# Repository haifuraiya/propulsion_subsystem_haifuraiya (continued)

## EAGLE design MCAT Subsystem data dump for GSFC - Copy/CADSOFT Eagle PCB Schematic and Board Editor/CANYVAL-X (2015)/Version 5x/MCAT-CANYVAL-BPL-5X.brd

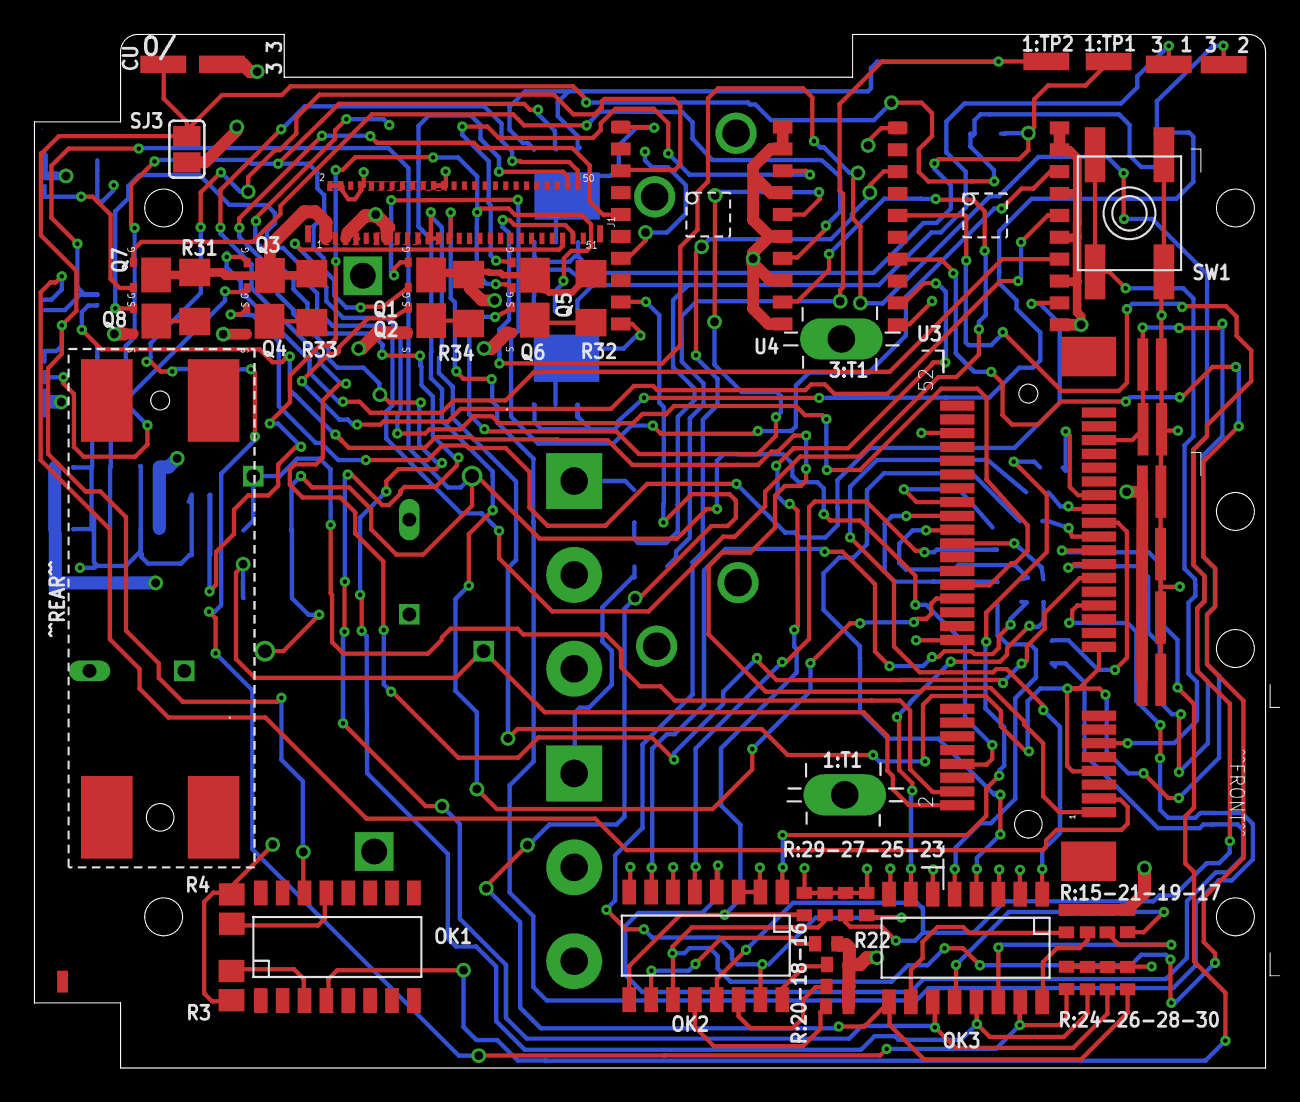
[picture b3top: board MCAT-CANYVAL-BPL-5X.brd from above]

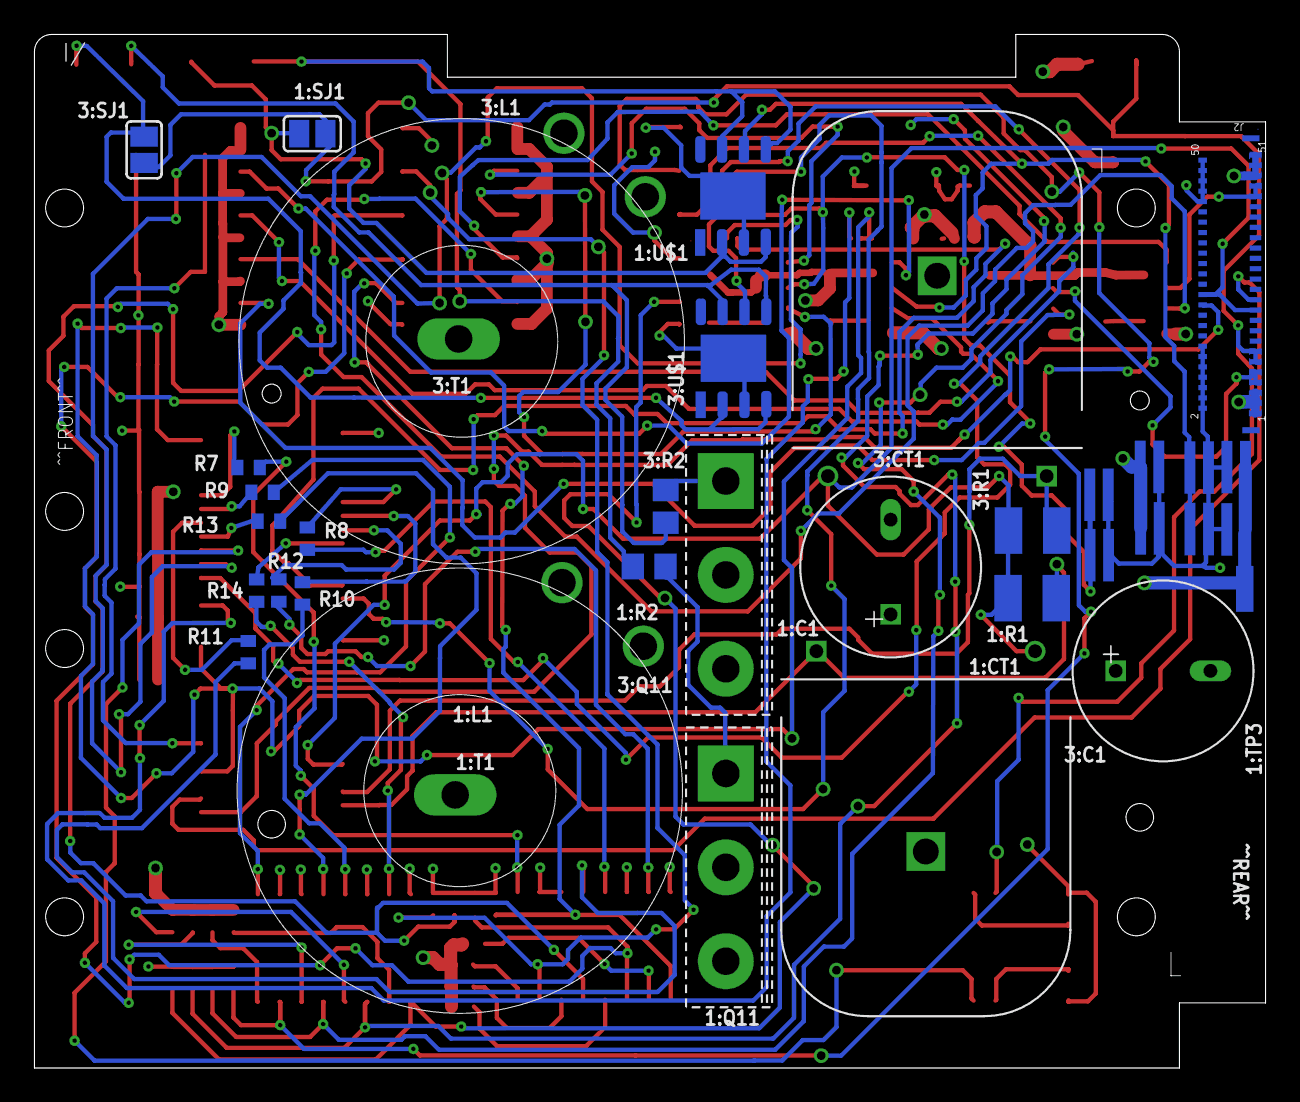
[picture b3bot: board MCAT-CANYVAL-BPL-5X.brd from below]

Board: 6 copper layers, 71.5 x 60.0 mm, 95 parts (34 on the bottom side), 78 nets.

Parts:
B2: MCAT-4CU-C-PCB/BPL; MCAT-4CU-C-BPL-V4-BLANK
CU-V2L1-1:BC3: BYPASS-CAP-1UF; 0612-REV
CU-V2L1-1:BC4: BYPASS-CAP-0.1UF; 0612-REV
CU-V2L1-1:J7: LATCH_NANO54415_MODULE; LATCH_SD-48099-400
CU-V2L1-1:J9: CONN_NANO54415_MODULE; CONN_SD-67910-001
CU-V2L1-1:OK1: PS2801C-4; SSOP(16PIN)
CU-V2L1-1:R3: 560R; R0805
CU-V2L1-1:R4: 1K2; R0805
CU-V2L1-1:SJ3: 0R; SJ
CU-V2L1-1:SW1: SPST_TACT-EVQQ2; EVQ-Q2
CU-V2L1-1:TP1: PCB-MINI-SMD-TESTPOINT/SQ; PCB-MINI-SMD-TESTPOINT
F1, F2, F3, F4, F5, F6: SMTRAM2-6-5-RA; SMTRA-M2-6-5-RA
J1, J2: MOLEX-502598-5193
PD-V2L1-1:BC1, PD-V2L1-1:BC4: BYPASS-CAP-0.1UF; 0612-REV
PD-V2L1-1:BC2, PD-V2L1-1:BC3: BYPASS-CAP-1UF; 0612-REV
PD-V2L1-1:OK2, PD-V2L1-1:OK3: PS2801C-4; SSOP(16PIN)
PD-V2L1-1:Q1, PD-V2L1-1:Q2, PD-V2L1-1:Q3, PD-V2L1-1:Q4, PD-V2L1-1:Q5, PD-V2L1-1:Q6, PD-V2L1-1:Q7, PD-V2L1-1:Q8: SI5404BDC; 1206-8-CHIPFET
PD-V2L1-1:R7, PD-V2L1-1:R8, PD-V2L1-1:R9, PD-V2L1-1:R10, PD-V2L1-1:R11, PD-V2L1-1:R12, PD-V2L1-1:R13: 5K42; R0402
PD-V2L1-1:R14: 5K42%; R0402
PD-V2L1-1:R15, PD-V2L1-1:R16, PD-V2L1-1:R17, PD-V2L1-1:R18, PD-V2L1-1:R19, PD-V2L1-1:R20, PD-V2L1-1:R21, PD-V2L1-1:R22: 100k; R0402
PD-V2L1-1:R23, PD-V2L1-1:R24, PD-V2L1-1:R25, PD-V2L1-1:R26, PD-V2L1-1:R27, PD-V2L1-1:R28, PD-V2L1-1:R29, PD-V2L1-1:R30: 51k; R0402
PD-V2L1-1:R31, PD-V2L1-1:R32, PD-V2L1-1:R33, PD-V2L1-1:R34: 0.1R; R1206
PD-V2L1-1:U3, PD-V2L1-1:U4: LT1161ISW; 20-LEAD-PLASTIC-SO
PPU-V8C1-1:BC1, PPU-V8C1-1:BC3, PPU-V8C1-3:BC1, PPU-V8C1-3:BC3: BYPASS-CAP-0.1UF; 0612-REV
PPU-V8C1-1:BC2, PPU-V8C1-1:BC4, PPU-V8C1-3:BC2, PPU-V8C1-3:BC4: BYPASS-CAP-1UF; 0612-REV
PPU-V8C1-1:C1, PPU-V8C1-3:C1: 680uF/20WV; CHEMI-CON-PSG-JB5
PPU-V8C1-1:CT1, PPU-V8C1-3:CT1: MURATA-5600-CURR-XFR/RA; MURATA-5600-SERIES-CURR-XFR-RA
PPU-V8C1-1:L1, PPU-V8C1-3:L1: PPUV8-INDUCTOR-V2
PPU-V8C1-1:Q11, PPU-V8C1-3:Q11: IXYH30N120C3D1; IXYS-TO-247-AD-VERT
PPU-V8C1-1:R1, PPU-V8C1-3:R1: 15R; R1210
PPU-V8C1-1:R2, PPU-V8C1-3:R2: 1K; R0805
PPU-V8C1-1:SJ1, PPU-V8C1-3:SJ1: 0R; SJ
PPU-V8C1-1:T1, PPU-V8C1-3:T1: MCAT-SPADE-TERMINAL; SPADE-TERMINAL-FLANGED-NYLON-INSULATED
PPU-V8C1-1:TP1, PPU-V8C1-1:TP2, PPU-V8C1-1:TP3, PPU-V8C1-3:TP1, PPU-V8C1-3:TP2, PPU-V8C1-3:TP3: PCB-MINI-SMD-TESTPOINT/SQ; PCB-MINI-SMD-TESTPOINT
PPU-V8C1-1:U$1, PPU-V8C1-3:U$1: IXDN604/SI; IXYS-SI-8PIN-POWER-SOIC

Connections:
AGND_ADC_GROUND: CU-V2L1-1:J9.8, J2.21, J2.24, PPU-V8C1-1:CT1.3, PPU-V8C1-1:R1.2, PPU-V8C1-3:CT1.3, PPU-V8C1-3:R1.2
CH1_P18H: PD-V2L1-1:Q2.S, PPU-V8C1-1:BC1.1, PPU-V8C1-1:BC2.1, PPU-V8C1-1:C1.POS, PPU-V8C1-1:L1.1, PPU-V8C1-1:TP3.1
CH1_P18L: PD-V2L1-1:Q1.S, PPU-V8C1-1:BC3.1, PPU-V8C1-1:BC4.1, PPU-V8C1-1:U$1.6
CH1_SENSE+: CU-V2L1-1:J9.2, PPU-V8C1-1:CT1.1, PPU-V8C1-1:R1.1
CH2_P18H: J2.1, J2.3, J2.5, PD-V2L1-1:Q4.S
CH2_P18L: J2.7, J2.9, PD-V2L1-1:Q3.S
CH2_SENSE+: CU-V2L1-1:J9.1, J2.22
CH3_P18H: PD-V2L1-1:Q6.S, PPU-V8C1-3:BC1.1, PPU-V8C1-3:BC2.1, PPU-V8C1-3:C1.POS, PPU-V8C1-3:L1.1, PPU-V8C1-3:TP3.1
CH3_P18L: PD-V2L1-1:Q5.S, PPU-V8C1-3:BC3.1, PPU-V8C1-3:BC4.1, PPU-V8C1-3:U$1.6
CH3_SENSE+: CU-V2L1-1:J9.4, PPU-V8C1-3:CT1.1, PPU-V8C1-3:R1.1
CH4_P18H: J2.47, J2.49, J2.51, PD-V2L1-1:Q8.S
CH4_P18L: J2.43, J2.45, PD-V2L1-1:Q7.S
CH4_SENSE+: CU-V2L1-1:J9.3, J2.23
CU-V2L1-1:!RSTI: CU-V2L1-1:J9.11, CU-V2L1-1:SW1.A, CU-V2L1-1:SW1.A'
CU-V2L1-1:N$1: CU-V2L1-1:OK1.3, CU-V2L1-1:R3.2
CU-V2L1-1:N$2: CU-V2L1-1:OK1.13, CU-V2L1-1:R4.2
CU-V2L1-1:SW_TP1: CU-V2L1-1:J9.31, CU-V2L1-1:OK1.4
GND: CU-V2L1-1:BC3.2, CU-V2L1-1:BC4.2, CU-V2L1-1:J9.18, CU-V2L1-1:J9.48, CU-V2L1-1:R3.1, CU-V2L1-1:R4.1, CU-V2L1-1:SW1.B, CU-V2L1-1:SW1.B', J1.2, J1.4, J1.8, J1.10, J1.12, J1.14, J1.16, J1.18, J1.20, J1.22, J1.24, J2.2, J2.4, J2.6, J2.8, J2.10, J2.12, J2.14, J2.42, J2.44, J2.46, J2.48, J2.50, PD-V2L1-1:BC1.2, PD-V2L1-1:BC2.2, PD-V2L1-1:BC3.2, PD-V2L1-1:BC4.2, PD-V2L1-1:OK2.2, PD-V2L1-1:OK2.3, PD-V2L1-1:OK2.6, PD-V2L1-1:OK2.8, PD-V2L1-1:OK3.2, PD-V2L1-1:OK3.3, PD-V2L1-1:OK3.6, PD-V2L1-1:OK3.8, PD-V2L1-1:R23.1, PD-V2L1-1:R24.1, PD-V2L1-1:R25.1, PD-V2L1-1:R26.1, PD-V2L1-1:R27.1, PD-V2L1-1:R28.1, PD-V2L1-1:R29.1, PD-V2L1-1:R30.1, PD-V2L1-1:U3.1, PD-V2L1-1:U3.10, PD-V2L1-1:U4.1, PD-V2L1-1:U4.10, PPU-V8C1-1:BC1.2, PPU-V8C1-1:BC2.2, PPU-V8C1-1:BC3.2, PPU-V8C1-1:BC4.2, PPU-V8C1-1:C1.NEG, PPU-V8C1-1:CT1.PPU-K, PPU-V8C1-1:Q11.E, PPU-V8C1-1:U$1.3, PPU-V8C1-1:U$1.9, PPU-V8C1-3:BC1.2, PPU-V8C1-3:BC2.2, PPU-V8C1-3:BC3.2, PPU-V8C1-3:BC4.2, PPU-V8C1-3:C1.NEG, PPU-V8C1-3:CT1.PPU-K, PPU-V8C1-3:Q11.E, PPU-V8C1-3:U$1.3, PPU-V8C1-3:U$1.9
MCAT_SCL: CU-V2L1-1:J9.27, J1.50
MCAT_SDA: CU-V2L1-1:J9.29, J1.49
unnamed: CU-V2L1-1:J9.33, PD-V2L1-1:R13.2
P3: CU-V2L1-1:BC3.1, CU-V2L1-1:BC4.1, CU-V2L1-1:J9.7, CU-V2L1-1:J9.17, CU-V2L1-1:J9.47, J1.21, J1.23
PD-V2L1-1:CH1HG: PD-V2L1-1:Q2.G, PD-V2L1-1:U3.16
PD-V2L1-1:CH1LG: PD-V2L1-1:Q1.G, PD-V2L1-1:U3.18
PD-V2L1-1:CH1S: PD-V2L1-1:Q2.D, PD-V2L1-1:R34.1
PD-V2L1-1:CH2HG: PD-V2L1-1:Q4.G, PD-V2L1-1:U3.12
PD-V2L1-1:CH2LG: PD-V2L1-1:Q3.G, PD-V2L1-1:U3.14
PD-V2L1-1:CH2S: PD-V2L1-1:Q4.D, PD-V2L1-1:R33.1
PD-V2L1-1:CH3HG: PD-V2L1-1:Q6.G, PD-V2L1-1:U4.16
PD-V2L1-1:CH3LG: PD-V2L1-1:Q5.G, PD-V2L1-1:U4.18
PD-V2L1-1:CH3S: PD-V2L1-1:Q6.D, PD-V2L1-1:R32.1
PD-V2L1-1:CH4HG: PD-V2L1-1:Q8.G, PD-V2L1-1:U4.12
PD-V2L1-1:CH4LG: PD-V2L1-1:Q7.G, PD-V2L1-1:U4.14
PD-V2L1-1:CH4S: PD-V2L1-1:Q8.D, PD-V2L1-1:R31.1
PD-V2L1-1:N$4: PD-V2L1-1:OK2.16, PD-V2L1-1:R16.2
PD-V2L1-1:N$5: PD-V2L1-1:OK2.14, PD-V2L1-1:R18.2
PD-V2L1-1:N$7: PD-V2L1-1:OK2.12, PD-V2L1-1:R20.2
PD-V2L1-1:N$9: PD-V2L1-1:OK2.10, PD-V2L1-1:R22.2
PD-V2L1-1:N$10: PD-V2L1-1:OK3.16, PD-V2L1-1:R21.2
PD-V2L1-1:N$11: PD-V2L1-1:OK3.14, PD-V2L1-1:R19.2
PD-V2L1-1:N$12: PD-V2L1-1:OK3.12, PD-V2L1-1:R17.2
PD-V2L1-1:N$13: PD-V2L1-1:OK3.10, PD-V2L1-1:R15.2
PD-V2L1-1:OK1E1: PD-V2L1-1:OK2.15, PD-V2L1-1:R23.2, PD-V2L1-1:U3.3
PD-V2L1-1:OK1E2: PD-V2L1-1:OK2.13, PD-V2L1-1:R25.2, PD-V2L1-1:U3.5
PD-V2L1-1:OK1E3: PD-V2L1-1:OK2.11, PD-V2L1-1:R27.2, PD-V2L1-1:U3.7
PD-V2L1-1:OK1E4: PD-V2L1-1:OK2.9, PD-V2L1-1:R29.2, PD-V2L1-1:U3.9
PD-V2L1-1:OK2E1: PD-V2L1-1:OK3.15, PD-V2L1-1:R24.2, PD-V2L1-1:U4.3
PD-V2L1-1:OK2E2: PD-V2L1-1:OK3.13, PD-V2L1-1:R26.2, PD-V2L1-1:U4.5
PD-V2L1-1:OK2E3: PD-V2L1-1:OK3.11, PD-V2L1-1:R28.2, PD-V2L1-1:U4.7
PD-V2L1-1:OK2E4: PD-V2L1-1:OK3.9, PD-V2L1-1:R30.2, PD-V2L1-1:U4.9
PD-V2L1-1:P18_SW1: PD-V2L1-1:OK2.1, PD-V2L1-1:R7.1
PD-V2L1-1:P18_SW2: PD-V2L1-1:OK2.5, PD-V2L1-1:R8.1
PD-V2L1-1:P18_SW3: PD-V2L1-1:OK3.1, PD-V2L1-1:R9.1
PD-V2L1-1:P18_SW4: PD-V2L1-1:OK3.5, PD-V2L1-1:R10.1
PD-V2L1-1:P18_SW5: PD-V2L1-1:OK2.4, PD-V2L1-1:R11.1
PD-V2L1-1:P18_SW6: PD-V2L1-1:OK2.7, PD-V2L1-1:R12.1
PD-V2L1-1:P18_SW7: PD-V2L1-1:OK3.4, PD-V2L1-1:R13.1
PD-V2L1-1:P18_SW8: PD-V2L1-1:OK3.7, PD-V2L1-1:R14.1
PPU-V8C1-1:N$2: PPU-V8C1-1:Q11.G, PPU-V8C1-1:R2.2
PPU-V8C1-1:PPU-A: PPU-V8C1-1:L1.2, PPU-V8C1-1:Q11.C, PPU-V8C1-1:T1.T
PPU-V8C1-1:TPIPD_IN: PPU-V8C1-1:SJ1.2, PPU-V8C1-1:TP1.1, PPU-V8C1-1:U$1.2, PPU-V8C1-1:U$1.4
PPU-V8C1-1:TPIPD_OUT: PPU-V8C1-1:R2.1, PPU-V8C1-1:TP2.1, PPU-V8C1-1:U$1.5, PPU-V8C1-1:U$1.7
PPU-V8C1-3:N$2: PPU-V8C1-3:Q11.G, PPU-V8C1-3:R2.2
PPU-V8C1-3:PPU-A: PPU-V8C1-3:L1.2, PPU-V8C1-3:Q11.C, PPU-V8C1-3:T1.T
PPU-V8C1-3:TPIPD_IN: PPU-V8C1-3:SJ1.2, PPU-V8C1-3:TP1.1, PPU-V8C1-3:U$1.2, PPU-V8C1-3:U$1.4
PPU-V8C1-3:TPIPD_OUT: PPU-V8C1-3:R2.1, PPU-V8C1-3:TP2.1, PPU-V8C1-3:U$1.5, PPU-V8C1-3:U$1.7
SW_P18H1: CU-V2L1-1:J9.35, PD-V2L1-1:R11.2
SW_P18H3: CU-V2L1-1:J9.34, PD-V2L1-1:R12.2
SW_P18H4: CU-V2L1-1:J9.32, PD-V2L1-1:R14.2
SW_P18L: CU-V2L1-1:J9.39, PD-V2L1-1:R7.2
SW_P18L2: CU-V2L1-1:J9.38, PD-V2L1-1:R8.2
SW_P18L3: CU-V2L1-1:J9.37, PD-V2L1-1:R9.2
SW_P18L4: CU-V2L1-1:J9.36, PD-V2L1-1:R10.2
SW_RUNPMA: CU-V2L1-1:J9.23, J1.25
TP1_OUT: CU-V2L1-1:OK1.14, CU-V2L1-1:SJ3.2, CU-V2L1-1:TP1.1, J2.11, J2.13, PPU-V8C1-1:SJ1.1, PPU-V8C1-3:SJ1.1
UART0_RX: CU-V2L1-1:J9.24, J1.48
UART0_TX: CU-V2L1-1:J9.26, J1.47
VOUTA: CU-V2L1-1:SJ3.1, J1.1, J1.3, J1.5, J1.7, J1.11, J1.13, J1.15, J1.17, J1.19, PD-V2L1-1:BC1.1, PD-V2L1-1:BC2.1, PD-V2L1-1:BC3.1, PD-V2L1-1:BC4.1, PD-V2L1-1:Q1.D, PD-V2L1-1:Q3.D, PD-V2L1-1:Q5.D, PD-V2L1-1:Q7.D, PD-V2L1-1:R15.1, PD-V2L1-1:R16.1, PD-V2L1-1:R17.1, PD-V2L1-1:R18.1, PD-V2L1-1:R19.1, PD-V2L1-1:R20.1, PD-V2L1-1:R21.1, PD-V2L1-1:R22.1, PD-V2L1-1:R31.2, PD-V2L1-1:R32.2, PD-V2L1-1:R33.2, PD-V2L1-1:R34.2, PD-V2L1-1:U3.11, PD-V2L1-1:U3.13, PD-V2L1-1:U3.15, PD-V2L1-1:U3.17, PD-V2L1-1:U3.19, PD-V2L1-1:U3.20, PD-V2L1-1:U4.11, PD-V2L1-1:U4.13, PD-V2L1-1:U4.15, PD-V2L1-1:U4.17, PD-V2L1-1:U4.19, PD-V2L1-1:U4.20

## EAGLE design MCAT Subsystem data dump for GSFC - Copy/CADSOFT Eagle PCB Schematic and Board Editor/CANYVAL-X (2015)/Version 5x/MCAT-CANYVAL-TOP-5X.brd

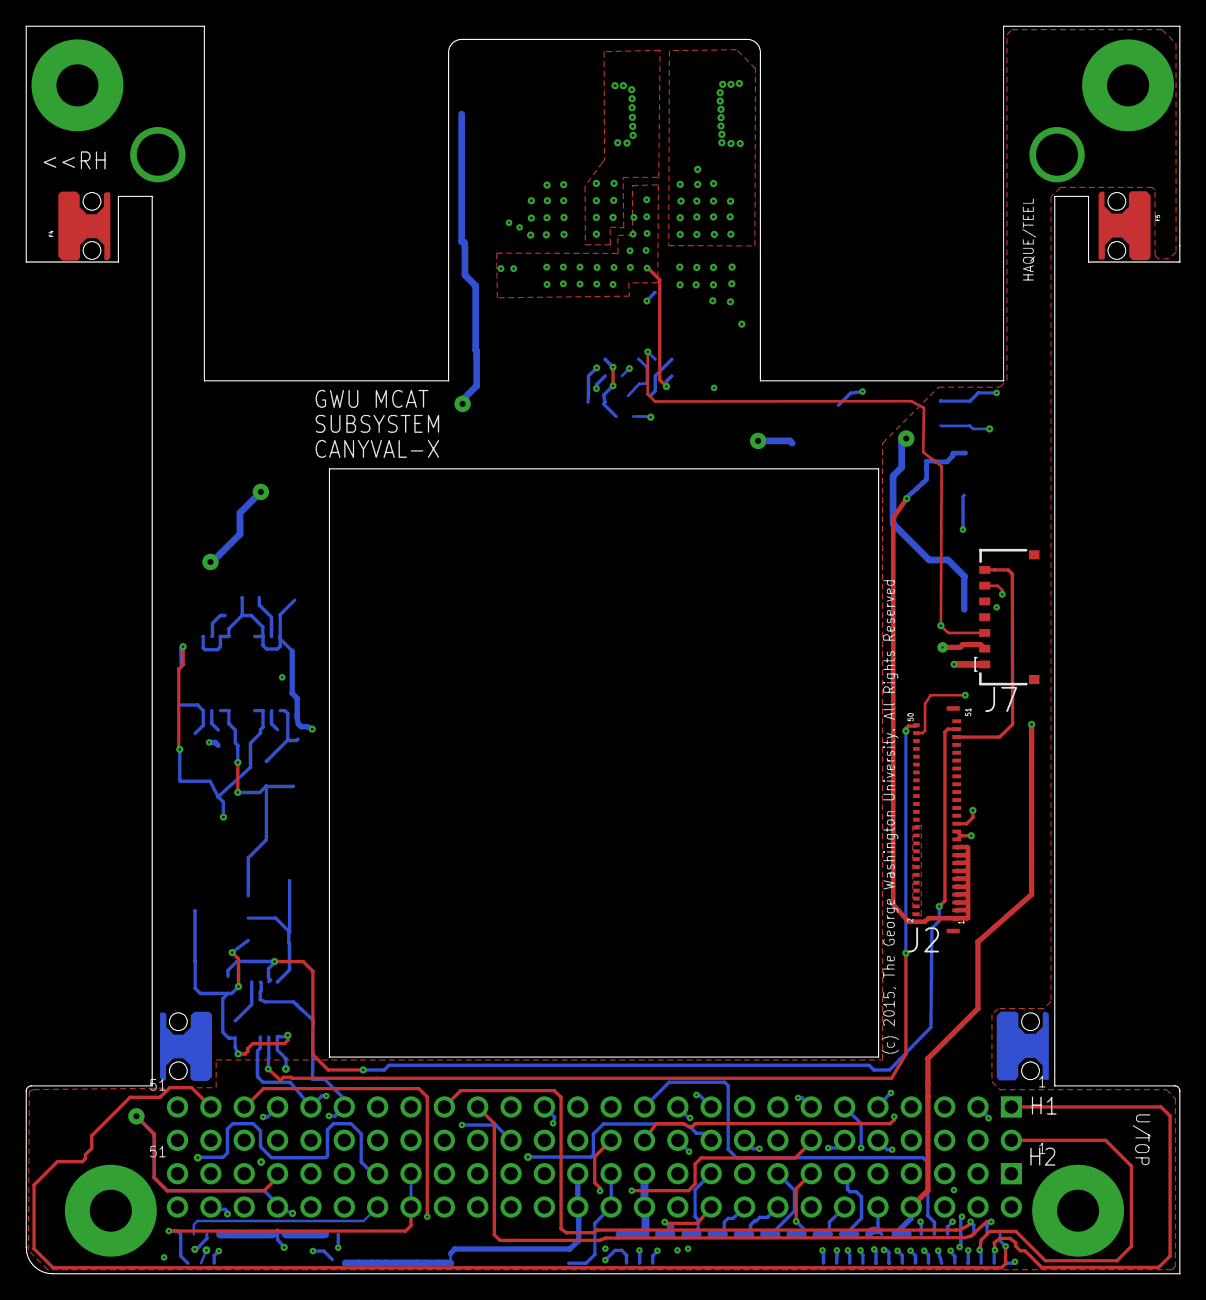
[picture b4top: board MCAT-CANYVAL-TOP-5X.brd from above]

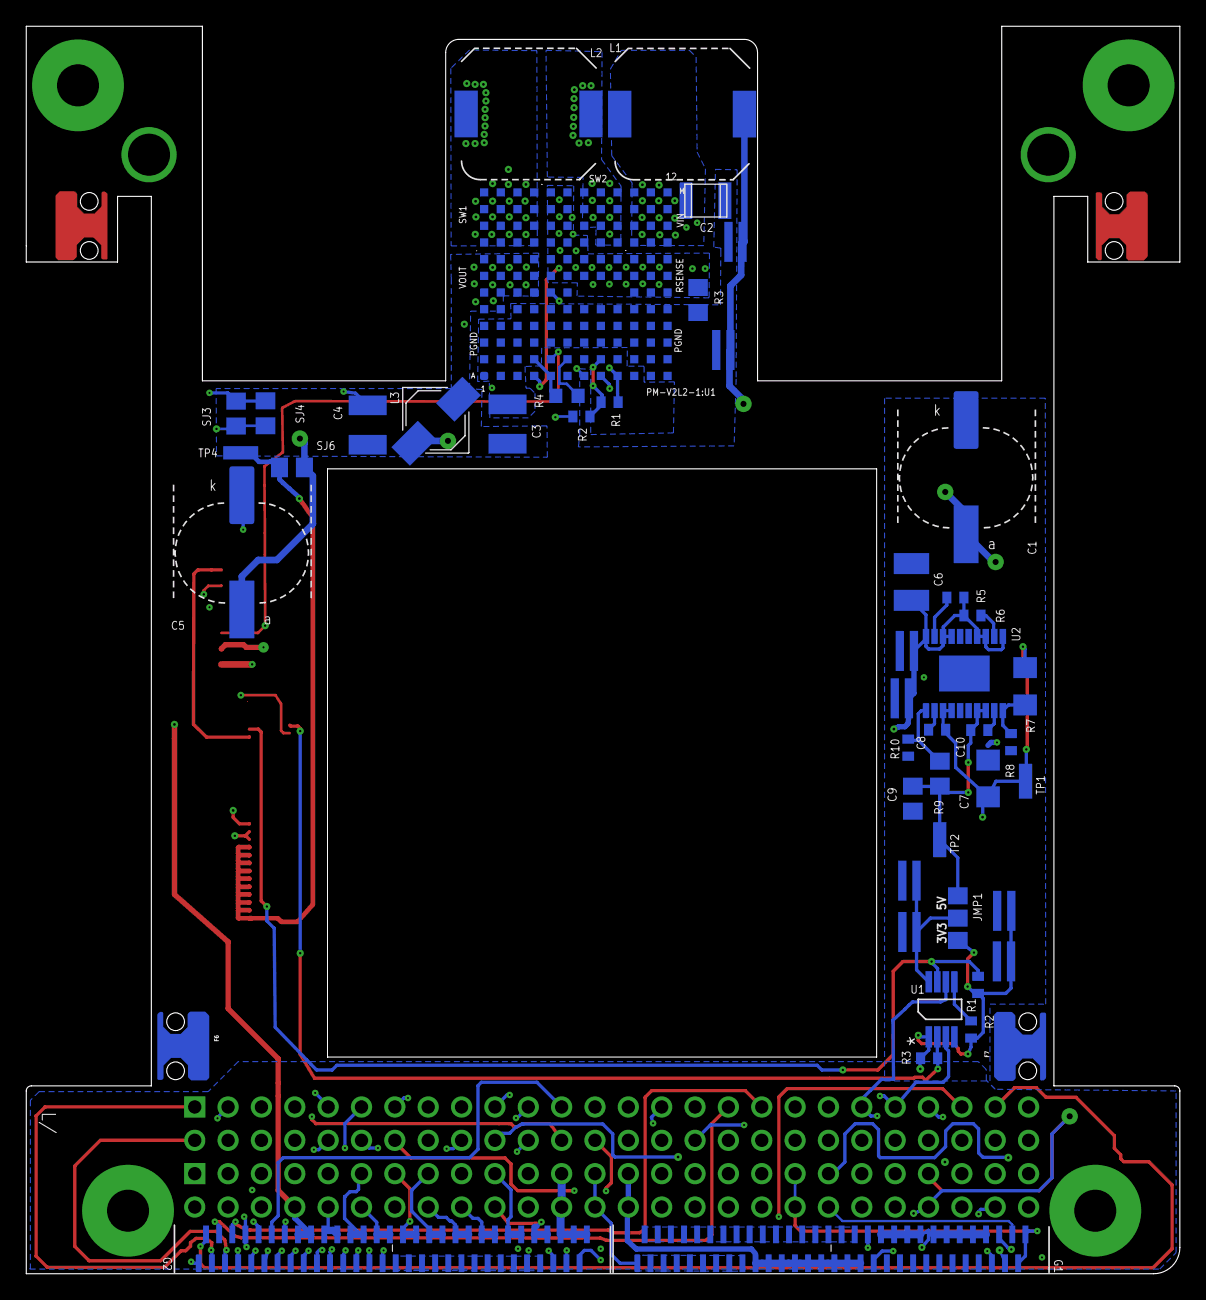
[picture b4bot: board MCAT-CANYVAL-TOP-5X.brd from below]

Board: 6 copper layers, 87.9 x 95.0 mm, 55 parts (48 on the bottom side), 72 nets.

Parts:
B8: MCAT-4CU-C-PCB/TOP; MCAT-4CU-C-TOP-V4-BLANK
CT-V2L1-1:BC3, CT-V2L1-1:BC5: BYPASS-CAP-1UF; 0612-REV
CT-V2L1-1:BC4, CT-V2L1-1:BC6: BYPASS-CAP-0.1UF; 0612-REV
CT-V2L1-1:J7: MOLEX-78171-5007
CT-V2L1-1:JMP1: 0R-JUMPA; A0R-JMP
CT-V2L1-1:R1, CT-V2L1-1:R2, CT-V2L1-1:R3: 10k; R0402
CT-V2L1-1:U1: PCA9512ADP; SOT505-1
F4, F5, F6, F7: SMTRAM2-6-5; SMTRA-M2-6-5
GBUS-TOP1:G1, GBUS-TOP1:G2: HIROSE-FH40-60S-0.5SV
GBUS-TOP1:H1: H1-H5-INBOARD-CSK-BUS-CONN; CONN-2X26X0.1-HDR
GBUS-TOP1:H2: H2-H6-OUTBOARD-CSK-BUS-CONN; CONN-2X26X0.1-HDR
J2: MOLEX-502598-5193
PM-V2L2-1:BC1, PM-V2L2-1:BC3: BYPASS-CAP-0.1UF; 0612-REV
PM-V2L2-1:BC2, PM-V2L2-1:BC4: BYPASS-CAP-1UF; 0612-REV
PM-V2L2-1:C1, PM-V2L2-1:C5: 68uF; OS-CON-SVPF-F12
PM-V2L2-1:C2: 4.7uF; MLCC-X7R-1210
PM-V2L2-1:C3, PM-V2L2-1:C4: 10uF; C1210K
PM-V2L2-1:C6: 10u; C1210
PM-V2L2-1:C7: 10u; C1206
PM-V2L2-1:C8, PM-V2L2-1:C10: 10n; C0402
PM-V2L2-1:C9: 3.3u; C0805
PM-V2L2-1:L1: 33uH; MSS1048
PM-V2L2-1:L2: 68uH; MSS1048
PM-V2L2-1:L3: 10uH; SERIES-POWER-INDUCTORS
PM-V2L2-1:R1: 2K; R0402
PM-V2L2-1:R2: 1K; R0402
PM-V2L2-1:R3: 27mOhms; R0805
PM-V2L2-1:R4: 4k70.1%; R0603
PM-V2L2-1:R5, PM-V2L2-1:R6: 1M; R0402
PM-V2L2-1:R7: 357K; R1206
PM-V2L2-1:R8: 210K; R0402
PM-V2L2-1:R9: 619K; R0805
PM-V2L2-1:R10: 200K; R0402
PM-V2L2-1:SJ3, PM-V2L2-1:SJ4, PM-V2L2-1:SJ6: 0R; R0805
PM-V2L2-1:TP1, PM-V2L2-1:TP2, PM-V2L2-1:TP4: PCB-MINI-SMD-TESTPOINT/SQ; PCB-MINI-SMD-TESTPOINT
PM-V2L2-1:U1: LTM4609MPV#PBF; LGA-141-LTC-05-08-1840-B
PM-V2L2-1:U2: LT3030MPFE#PBF; TSSOP20-FE-CB

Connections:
CT-V2L1-1:I2C_VCC: CT-V2L1-1:BC5.1, CT-V2L1-1:BC6.1, CT-V2L1-1:JMP1.2, CT-V2L1-1:U1.8
CT-V2L1-1:N$2: CT-V2L1-1:R2.1, CT-V2L1-1:U1.5
GBUS-TOP1:G-H1-1: GBUS-TOP1:G2.2, GBUS-TOP1:H1.1
GBUS-TOP1:G-H1-2: GBUS-TOP1:G2.3, GBUS-TOP1:H1.2
GBUS-TOP1:G-H1-3: GBUS-TOP1:G2.4, GBUS-TOP1:H1.3
GBUS-TOP1:G-H1-9: GBUS-TOP1:G2.5, GBUS-TOP1:H1.9
GBUS-TOP1:G-H1-10: GBUS-TOP1:G2.6, GBUS-TOP1:H1.10
GBUS-TOP1:G-H1-11: GBUS-TOP1:G2.7, GBUS-TOP1:H1.11
GBUS-TOP1:G-H1-12: GBUS-TOP1:G2.8, GBUS-TOP1:H1.12
GBUS-TOP1:G-H1-13: GBUS-TOP1:G2.9, GBUS-TOP1:H1.13
GBUS-TOP1:G-H1-14: GBUS-TOP1:G2.10, GBUS-TOP1:H1.14
GBUS-TOP1:G-H1-18: GBUS-TOP1:G2.28, GBUS-TOP1:H1.18
GBUS-TOP1:G-H1-19: GBUS-TOP1:G1.28, GBUS-TOP1:H1.19
GBUS-TOP1:G-H1-20: GBUS-TOP1:G1.29, GBUS-TOP1:H1.20
GBUS-TOP1:G-H1-21: GBUS-TOP1:G2.34, GBUS-TOP1:H1.21
GBUS-TOP1:G-H1-22: GBUS-TOP1:G2.35, GBUS-TOP1:H1.22
GBUS-TOP1:G-H1-23: GBUS-TOP1:G2.36, GBUS-TOP1:H1.23
GBUS-TOP1:G-H1-24: GBUS-TOP1:G2.11, GBUS-TOP1:H1.24
GBUS-TOP1:G-H1-26: GBUS-TOP1:G2.29, GBUS-TOP1:H1.26
GBUS-TOP1:G-H1-29: GBUS-TOP1:G2.30, GBUS-TOP1:H1.29
GBUS-TOP1:G-H1-33: GBUS-TOP1:G2.32, GBUS-TOP1:H1.33
GBUS-TOP1:G-H1-35: GBUS-TOP1:G2.33, GBUS-TOP1:H1.35
GBUS-TOP1:G-H1-45: GBUS-TOP1:G2.14, GBUS-TOP1:H1.45
GBUS-TOP1:G-H1-47: GBUS-TOP1:G2.15, GBUS-TOP1:H1.47
GBUS-TOP1:G-H1-49: GBUS-TOP1:G2.31, GBUS-TOP1:H1.49
GBUS-TOP1:G-H2-50: GBUS-TOP1:G2.1, GBUS-TOP1:H2.50
GBUS-TOP1:M-3V3-BUS: GBUS-TOP1:G1.10, GBUS-TOP1:G1.11, GBUS-TOP1:G1.12, GBUS-TOP1:G1.13, GBUS-TOP1:G1.14, GBUS-TOP1:G1.15, GBUS-TOP1:G1.16, GBUS-TOP1:G1.17, GBUS-TOP1:G1.18, GBUS-TOP1:H2.27, GBUS-TOP1:H2.28
GBUS-TOP1:M-5V-BUS: GBUS-TOP1:G1.1, GBUS-TOP1:G1.2, GBUS-TOP1:G1.3, GBUS-TOP1:G1.4, GBUS-TOP1:G1.5, GBUS-TOP1:G1.6, GBUS-TOP1:G1.7, GBUS-TOP1:G1.8, GBUS-TOP1:G1.9, GBUS-TOP1:H2.25, GBUS-TOP1:H2.26
GBUS-TOP1:M-5V-USB-CHG: GBUS-TOP1:G1.48, GBUS-TOP1:H1.32
GBUS-TOP1:M-12V-BUS: GBUS-TOP1:G2.58, GBUS-TOP1:G2.59, GBUS-TOP1:G2.60, GBUS-TOP1:H2.23, GBUS-TOP1:H2.24
GBUS-TOP1:M-SW2-12V: GBUS-TOP1:G2.40, GBUS-TOP1:G2.41, GBUS-TOP1:H2.10
GBUS-TOP1:M-SW3-BAT: GBUS-TOP1:G2.42, GBUS-TOP1:G2.43, GBUS-TOP1:H2.11
GBUS-TOP1:M-SW4-BAT: GBUS-TOP1:G2.44, GBUS-TOP1:G2.45, GBUS-TOP1:H2.12
GBUS-TOP1:M-SW5-5V: GBUS-TOP1:G2.46, GBUS-TOP1:G2.47, GBUS-TOP1:H2.13
GBUS-TOP1:M-SW6-5V: GBUS-TOP1:G2.48, GBUS-TOP1:G2.49, GBUS-TOP1:H2.15
GBUS-TOP1:M-SW7-5V: GBUS-TOP1:G2.50, GBUS-TOP1:G2.51, GBUS-TOP1:H2.16
GBUS-TOP1:M-SW8-3V3: GBUS-TOP1:G2.52, GBUS-TOP1:G2.53, GBUS-TOP1:H2.18
GBUS-TOP1:M-SW9-3V3: GBUS-TOP1:G2.54, GBUS-TOP1:G2.55, GBUS-TOP1:H2.19
GBUS-TOP1:M-SW10-3V3: GBUS-TOP1:G2.56, GBUS-TOP1:G2.57, GBUS-TOP1:H2.20
GBUS-TOP1:RBF_SW: GBUS-TOP1:G1.30, GBUS-TOP1:G1.60, GBUS-TOP1:H2.37, GBUS-TOP1:H2.38
GBUS-TOP1:SEP_SW1: GBUS-TOP1:G1.58, GBUS-TOP1:H2.39
GBUS-TOP1:SEP_SW2: GBUS-TOP1:G1.59, GBUS-TOP1:H2.40
GND: B8.GND, B8.GND@1, B8.GND@2, B8.GND@3, B8.GND@4, B8.GND@6, CT-V2L1-1:BC3.2, CT-V2L1-1:BC4.2, CT-V2L1-1:BC5.2, CT-V2L1-1:BC6.2, CT-V2L1-1:J7.5, CT-V2L1-1:U1.4, GBUS-TOP1:G1.19, GBUS-TOP1:G1.20, GBUS-TOP1:G1.21, GBUS-TOP1:G1.22, GBUS-TOP1:G1.23, GBUS-TOP1:G1.24, GBUS-TOP1:G1.25, GBUS-TOP1:G1.26, GBUS-TOP1:G1.27, GBUS-TOP1:G1.31, GBUS-TOP1:G1.32, GBUS-TOP1:G1.33, GBUS-TOP1:G1.34, GBUS-TOP1:G1.35, GBUS-TOP1:G1.36, GBUS-TOP1:G1.37, GBUS-TOP1:G1.38, GBUS-TOP1:G1.39, GBUS-TOP1:G1.40, GBUS-TOP1:G1.41, GBUS-TOP1:G1.42, GBUS-TOP1:G1.43, GBUS-TOP1:G1.44, GBUS-TOP1:G1.45, GBUS-TOP1:G1.46, GBUS-TOP1:G1.47, GBUS-TOP1:G2.16, GBUS-TOP1:G2.17, GBUS-TOP1:G2.18, GBUS-TOP1:G2.19, GBUS-TOP1:G2.20, GBUS-TOP1:G2.21, GBUS-TOP1:G2.22, GBUS-TOP1:G2.23, GBUS-TOP1:G2.24, GBUS-TOP1:G2.25, GBUS-TOP1:G2.26, GBUS-TOP1:G2.27, GBUS-TOP1:G2.37, GBUS-TOP1:H2.9, GBUS-TOP1:H2.14, GBUS-TOP1:H2.17, GBUS-TOP1:H2.21, GBUS-TOP1:H2.22, GBUS-TOP1:H2.29, GBUS-TOP1:H2.30, GBUS-TOP1:H2.32, GBUS-TOP1:H2.47, GBUS-TOP1:H2.48, J2.2, J2.4, J2.6, J2.8, J2.10, J2.12, J2.14, J2.16, J2.18, J2.20, J2.22, J2.24, PM-V2L2-1:BC1.2, PM-V2L2-1:BC2.2, PM-V2L2-1:BC3.2, PM-V2L2-1:BC4.2, PM-V2L2-1:C1.K1, PM-V2L2-1:C2.2, PM-V2L2-1:C3.2, PM-V2L2-1:C4.2, PM-V2L2-1:C5.K1, PM-V2L2-1:C6.2, PM-V2L2-1:C7.2, PM-V2L2-1:C9.2, PM-V2L2-1:R3.2, PM-V2L2-1:R4.1, PM-V2L2-1:R8.1, PM-V2L2-1:R10.1, PM-V2L2-1:SJ3.1, PM-V2L2-1:SJ4.1, PM-V2L2-1:U1.A1, PM-V2L2-1:U1.A2, PM-V2L2-1:U1.A3, PM-V2L2-1:U1.A5, PM-V2L2-1:U1.A11, PM-V2L2-1:U1.A12, PM-V2L2-1:U1.B1, PM-V2L2-1:U1.B2, PM-V2L2-1:U1.B3, PM-V2L2-1:U1.B4, PM-V2L2-1:U1.B10, PM-V2L2-1:U1.B11, PM-V2L2-1:U1.B12, PM-V2L2-1:U1.C1, PM-V2L2-1:U1.C2, PM-V2L2-1:U1.C3, PM-V2L2-1:U1.C4, PM-V2L2-1:U1.C5, PM-V2L2-1:U1.C6, PM-V2L2-1:U1.C7, PM-V2L2-1:U1.C8, PM-V2L2-1:U1.C9, PM-V2L2-1:U1.C10, PM-V2L2-1:U1.C11, PM-V2L2-1:U1.C12, PM-V2L2-1:U1.D1, PM-V2L2-1:U1.D2, PM-V2L2-1:U1.D3, PM-V2L2-1:U1.D4, PM-V2L2-1:U1.D5, PM-V2L2-1:U1.D6, PM-V2L2-1:U1.D7, PM-V2L2-1:U1.D8, PM-V2L2-1:U1.D9, PM-V2L2-1:U1.D10, PM-V2L2-1:U1.D11, PM-V2L2-1:U1.D12, PM-V2L2-1:U1.E3, PM-V2L2-1:U1.E4, PM-V2L2-1:U1.E5, PM-V2L2-1:U1.E6, PM-V2L2-1:U1.E7, PM-V2L2-1:U1.E8, PM-V2L2-1:U1.E9, PM-V2L2-1:U1.E10, PM-V2L2-1:U1.E11, PM-V2L2-1:U1.E12, PM-V2L2-1:U2.5, PM-V2L2-1:U2.6, PM-V2L2-1:U2.15, PM-V2L2-1:U2.16, PM-V2L2-1:U2.21
MCAT_SCL: CT-V2L1-1:R3.1, CT-V2L1-1:U1.2, J2.50
MCAT_SDA: CT-V2L1-1:R1.1, CT-V2L1-1:U1.7, J2.49
P3: CT-V2L1-1:BC3.1, CT-V2L1-1:BC4.1, CT-V2L1-1:JMP1.1, CT-V2L1-1:R1.2, CT-V2L1-1:R2.2, CT-V2L1-1:R3.2, CT-V2L1-1:U1.1, J2.21, J2.23, PM-V2L2-1:C7.1, PM-V2L2-1:C8.1, PM-V2L2-1:R7.2, PM-V2L2-1:TP1.1, PM-V2L2-1:U2.3, PM-V2L2-1:U2.4
P5: CT-V2L1-1:JMP1.3, PM-V2L2-1:C9.1, PM-V2L2-1:C10.1, PM-V2L2-1:R9.2, PM-V2L2-1:TP2.1, PM-V2L2-1:U2.7, PM-V2L2-1:U2.8
P12_IN: CT-V2L1-1:J7.2, GBUS-TOP1:G2.38, GBUS-TOP1:G2.39, GBUS-TOP1:H2.8, PM-V2L2-1:BC1.1, PM-V2L2-1:BC2.1, PM-V2L2-1:C6.1, PM-V2L2-1:R5.2, PM-V2L2-1:R6.2, PM-V2L2-1:U2.11, PM-V2L2-1:U2.13, PM-V2L2-1:U2.14, PM-V2L2-1:U2.17, PM-V2L2-1:U2.18, PM-V2L2-1:U2.20
PGOOD_PMA: CT-V2L1-1:J7.3, PM-V2L2-1:U1.B5
PM-V2L2-1:ADJ1: PM-V2L2-1:R9.1, PM-V2L2-1:R10.2, PM-V2L2-1:U2.1
PM-V2L2-1:ADJ2: PM-V2L2-1:R7.1, PM-V2L2-1:R8.2, PM-V2L2-1:U2.10
PM-V2L2-1:BYP1: PM-V2L2-1:C8.2, PM-V2L2-1:U2.2
PM-V2L2-1:BYP2: PM-V2L2-1:C10.2, PM-V2L2-1:U2.9
PM-V2L2-1:INTVCC: PM-V2L2-1:R1.1, PM-V2L2-1:U1.A9, PM-V2L2-1:U1.F5
PM-V2L2-1:P18_OUT: PM-V2L2-1:C5.A1, PM-V2L2-1:L3.2, PM-V2L2-1:SJ6.1
PM-V2L2-1:PWRDGD2: PM-V2L2-1:R6.1, PM-V2L2-1:U2.12
PM-V2L2-1:PWRGD1: PM-V2L2-1:R5.1, PM-V2L2-1:U2.19
PM-V2L2-1:RSENSE: PM-V2L2-1:R3.1, PM-V2L2-1:U1.A4, PM-V2L2-1:U1.F10, PM-V2L2-1:U1.F11, PM-V2L2-1:U1.F12, PM-V2L2-1:U1.G5, PM-V2L2-1:U1.G6, PM-V2L2-1:U1.G7, PM-V2L2-1:U1.G8, PM-V2L2-1:U1.G9, PM-V2L2-1:U1.G10, PM-V2L2-1:U1.G11, PM-V2L2-1:U1.G12, PM-V2L2-1:U1.H5, PM-V2L2-1:U1.H6, PM-V2L2-1:U1.H7, PM-V2L2-1:U1.H8, PM-V2L2-1:U1.H9, PM-V2L2-1:U1.H10, PM-V2L2-1:U1.H11, PM-V2L2-1:U1.H12, PM-V2L2-1:U1.J5, PM-V2L2-1:U1.J6, PM-V2L2-1:U1.J7, PM-V2L2-1:U1.K5, PM-V2L2-1:U1.K6, PM-V2L2-1:U1.L5, PM-V2L2-1:U1.L6, PM-V2L2-1:U1.M5, PM-V2L2-1:U1.M6
PM-V2L2-1:SETFREQ: PM-V2L2-1:R1.2, PM-V2L2-1:R2.1, PM-V2L2-1:U1.B8
PM-V2L2-1:SGND: PM-V2L2-1:R2.2, PM-V2L2-1:SJ3.2, PM-V2L2-1:SJ4.2, PM-V2L2-1:U1.A7
PM-V2L2-1:SW1: PM-V2L2-1:L2.2, PM-V2L2-1:U1.SW1@J1, PM-V2L2-1:U1.SW1@J2, PM-V2L2-1:U1.SW1@J3, PM-V2L2-1:U1.SW1@J4, PM-V2L2-1:U1.SW1@K1, PM-V2L2-1:U1.SW1@K2, PM-V2L2-1:U1.SW1@K3, PM-V2L2-1:U1.SW1@K4, PM-V2L2-1:U1.SW1@L1, PM-V2L2-1:U1.SW1@L2, PM-V2L2-1:U1.SW1@L3, PM-V2L2-1:U1.SW1@L4, PM-V2L2-1:U1.SW1@M1, PM-V2L2-1:U1.SW1@M2, PM-V2L2-1:U1.SW1@M3, PM-V2L2-1:U1.SW1@M4
PM-V2L2-1:SW2: PM-V2L2-1:L2.1, PM-V2L2-1:U1.J8, PM-V2L2-1:U1.J9, PM-V2L2-1:U1.K7, PM-V2L2-1:U1.K8, PM-V2L2-1:U1.K9, PM-V2L2-1:U1.L7, PM-V2L2-1:U1.L8, PM-V2L2-1:U1.L9, PM-V2L2-1:U1.M7, PM-V2L2-1:U1.M8, PM-V2L2-1:U1.M9
PM-V2L2-1:VFB: PM-V2L2-1:R4.2, PM-V2L2-1:U1.B6
PM-V2L2-1:VIN: PM-V2L2-1:C2.1, PM-V2L2-1:L1.2, PM-V2L2-1:U1.J10, PM-V2L2-1:U1.J11, PM-V2L2-1:U1.J12, PM-V2L2-1:U1.K10, PM-V2L2-1:U1.K11, PM-V2L2-1:U1.K12, PM-V2L2-1:U1.L10, PM-V2L2-1:U1.L11, PM-V2L2-1:U1.L12, PM-V2L2-1:U1.M10, PM-V2L2-1:U1.M11, PM-V2L2-1:U1.M12
PM-V2L2-1:VOUT: PM-V2L2-1:C3.1, PM-V2L2-1:C4.1, PM-V2L2-1:L3.1, PM-V2L2-1:U1.E1, PM-V2L2-1:U1.E2, PM-V2L2-1:U1.F1, PM-V2L2-1:U1.F2, PM-V2L2-1:U1.F3, PM-V2L2-1:U1.F4, PM-V2L2-1:U1.G1, PM-V2L2-1:U1.G2, PM-V2L2-1:U1.G3, PM-V2L2-1:U1.G4, PM-V2L2-1:U1.H2, PM-V2L2-1:U1.H3, PM-V2L2-1:U1.H4, PM-V2L2-1:U1.VOUT
SCLIN: CT-V2L1-1:U1.3, GBUS-TOP1:G2.13, GBUS-TOP1:H1.43
SDAIN: CT-V2L1-1:U1.6, GBUS-TOP1:G2.12, GBUS-TOP1:H1.41
SW_RUNPMA: J2.25, PM-V2L2-1:U1.A8
UART0_RX: CT-V2L1-1:J7.6, J2.48
UART0_TX: CT-V2L1-1:J7.7, J2.47
VBATT_IN: CT-V2L1-1:J7.1, GBUS-TOP1:G1.49, GBUS-TOP1:G1.50, GBUS-TOP1:G1.51, GBUS-TOP1:G1.52, GBUS-TOP1:G1.53, GBUS-TOP1:G1.54, GBUS-TOP1:G1.55, GBUS-TOP1:G1.56, GBUS-TOP1:G1.57, GBUS-TOP1:H2.45, GBUS-TOP1:H2.46, PM-V2L2-1:BC3.1, PM-V2L2-1:BC4.1, PM-V2L2-1:C1.A1, PM-V2L2-1:L1.1
VOUTA: J2.1, J2.3, J2.5, J2.7, J2.9, J2.11, J2.13, J2.15, J2.17, J2.19, PM-V2L2-1:SJ6.2, PM-V2L2-1:TP4.1

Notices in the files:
parts and their libraries:
COPYRIGHT: (c) 2015, The George Washington University. All Rights Reserved.
